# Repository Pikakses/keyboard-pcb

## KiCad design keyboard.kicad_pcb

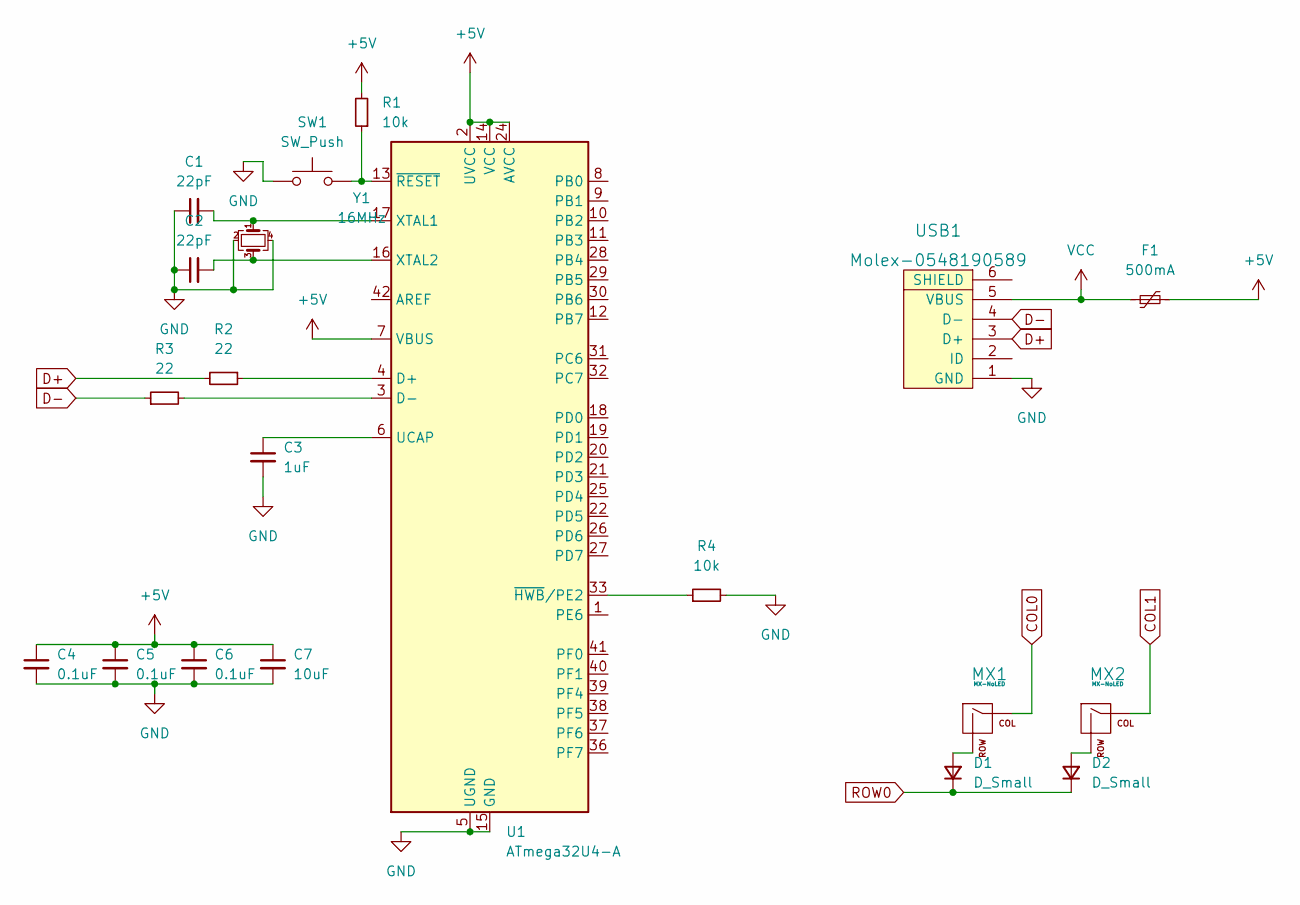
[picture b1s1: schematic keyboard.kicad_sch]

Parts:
C1, C2: 22pF; C_0805_2012Metric
C3: 1uF; C_0805_2012Metric
C4, C5, C6: 0.1uF; C_0805_2012Metric
C7: 10uF; C_0805_2012Metric
D1, D2: D_Small; D_SOD-123
F1: 500mA; Fuse_1206_3216Metric
MX1, MX2: MX-NoLED; MX-1U
R1, R4: 10k; R_0805_2012Metric
R2, R3: 22; R_0805_2012Metric
SW1: SW_Push; SKQG-1155865
U1: ATmega32U4-A; TQFP-44_10x10mm_P0.8mm
USB1: Molex-0548190589
Y1: 16MHz; Crystal_SMD_3225-4Pin_3.2x2.5mm

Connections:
+5V: C4.1, C5.1, C6.1, C7.1, F1.2, R1.2, U1.2 (UVCC), U1.7 (VBUS), U1.14 (VCC), U1.24 (AVCC), U1.34 (VCC), U1.44 (AVCC)
COL0: MX1.1 (COL)
COL1: MX2.1 (COL)
D+: R2.2, USB1.3 (D+)
D-: R3.1, USB1.4 (D-)
GND: C1.1, C2.1, C3.2, C4.2, C5.2, C6.2, C7.2, R4.2, SW1.1, U1.5 (UGND), U1.15 (GND), U1.23 (GND), U1.35 (GND), U1.43 (GND), USB1.1 (GND), Y1.2, Y1.4
unnamed: C1.2, U1.17 (XTAL1), Y1.1
unnamed: C2.2, U1.16 (XTAL2), Y1.3
unnamed: C3.1, U1.6 (UCAP)
unnamed: D1.2 (A), MX1.2 (ROW)
unnamed: D2.2 (A), MX2.2 (ROW)
unnamed: R1.1, SW1.2, U1.13 (~RESET)
unnamed: R2.1, U1.4 (D+)
unnamed: R3.2, U1.3 (D-)
unnamed: R4.1, U1.33 (~HWB/PE2)
ROW0: D1.1 (K), D2.1 (K)
VCC: F1.1, USB1.5 (VBUS)

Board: 2 copper layers, 20 parts (15 on the bottom side), 15 nets, no tracks yet.

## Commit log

2022-06-29 main files
2022-06-29 Add submodules
2022-06-29 add libraries
2022-06-29 schematic
2022-06-29 pcb schematic
